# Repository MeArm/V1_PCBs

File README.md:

# V1_PCBs
Here we have the PCBs for the original controllers for the version 1 MeArm, including sliders and joysticks

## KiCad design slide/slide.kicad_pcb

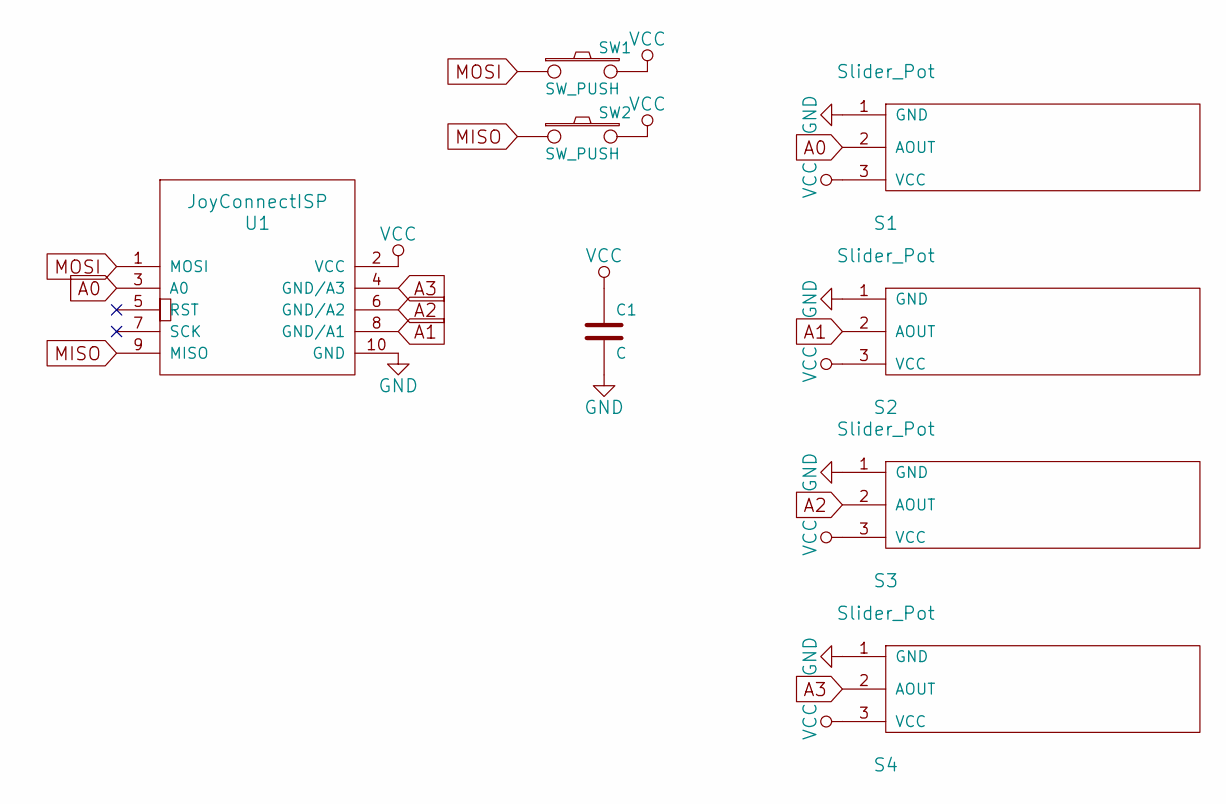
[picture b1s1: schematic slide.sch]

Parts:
C1: C; C_Disc_D3_P2.5
S1, S2, S3, S4: Slider_Pot; Slider_Potentiometer
SW1, SW2: SW_PUSH; TacSwitch
U1: JoyConnectISP; Pin_Header_Straight_2x05

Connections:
A0: S1.2 (AOUT), U1.3 (A0)
A1: S2.2 (AOUT), U1.8 (GND/A1)
A2: S3.2 (AOUT), U1.6 (GND/A2)
A3: S4.2 (AOUT), U1.4 (GND/A3)
GND: C1.2, S1.1 (GND), S2.1 (GND), S3.1 (GND), S4.1 (GND), U1.10 (GND)
MISO: SW2.1, U1.9 (MISO)
MOSI: SW1.1, U1.1 (MOSI)
VCC: C1.1, S1.3 (VCC), S2.3 (VCC), S3.3 (VCC), S4.3 (VCC), SW1.2, SW2.2, U1.2 (VCC)

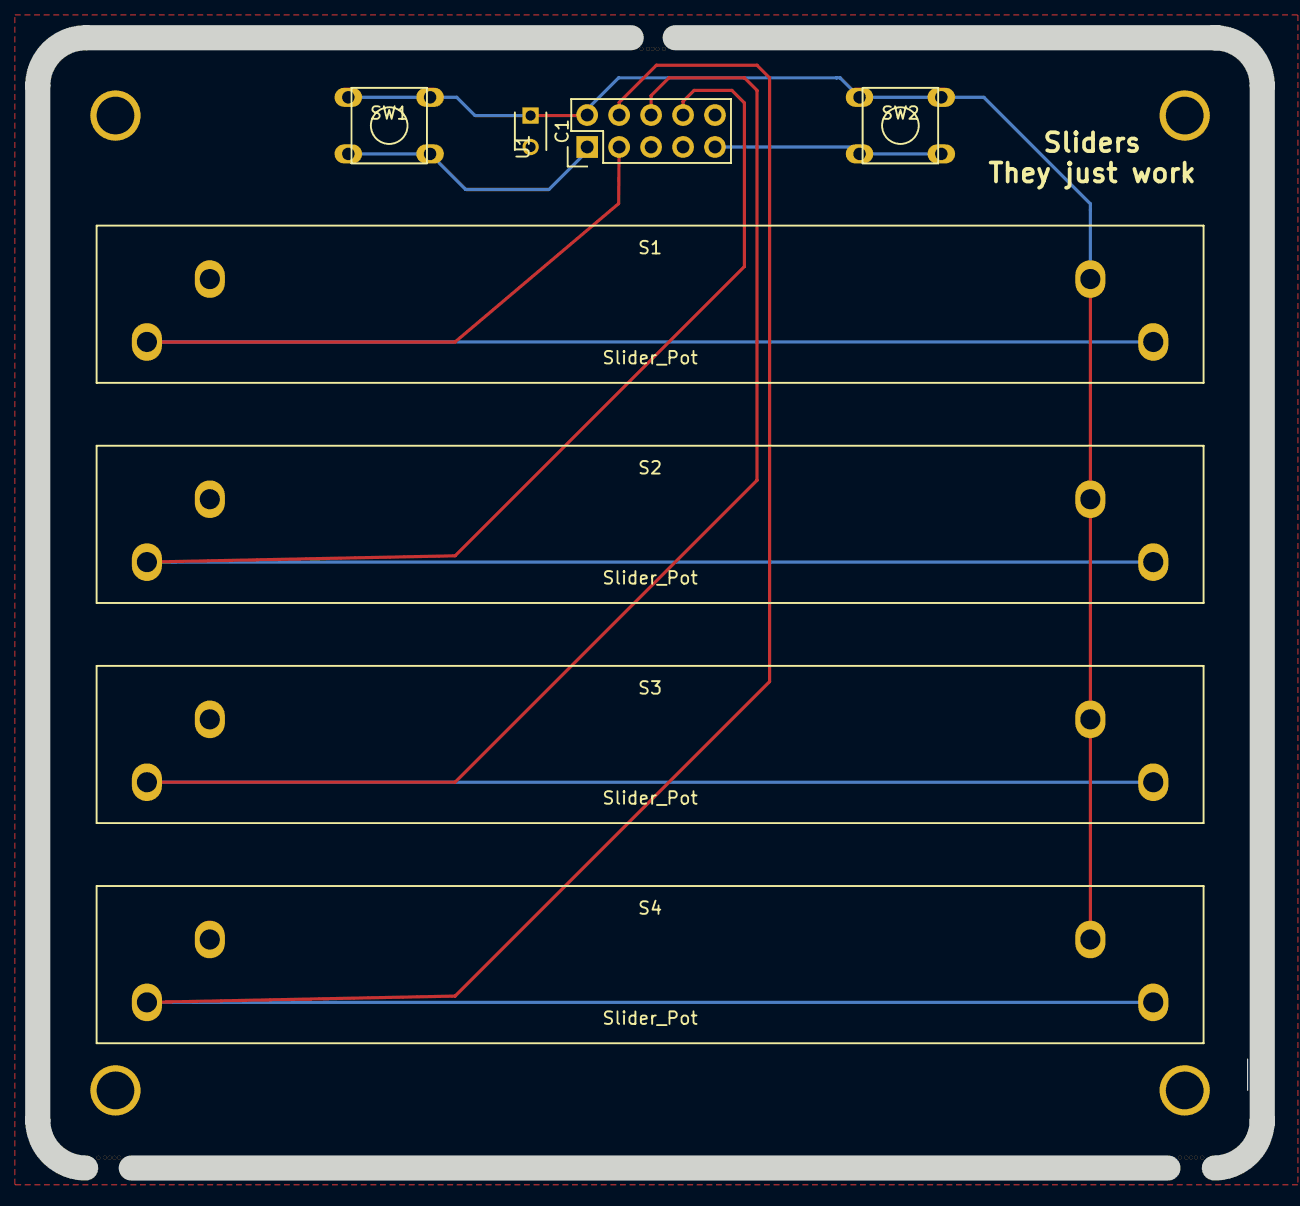
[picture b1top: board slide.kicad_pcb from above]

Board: 2 copper layers, 97.3 x 89.9 mm, 8 parts (0 on the bottom side), 8 nets.

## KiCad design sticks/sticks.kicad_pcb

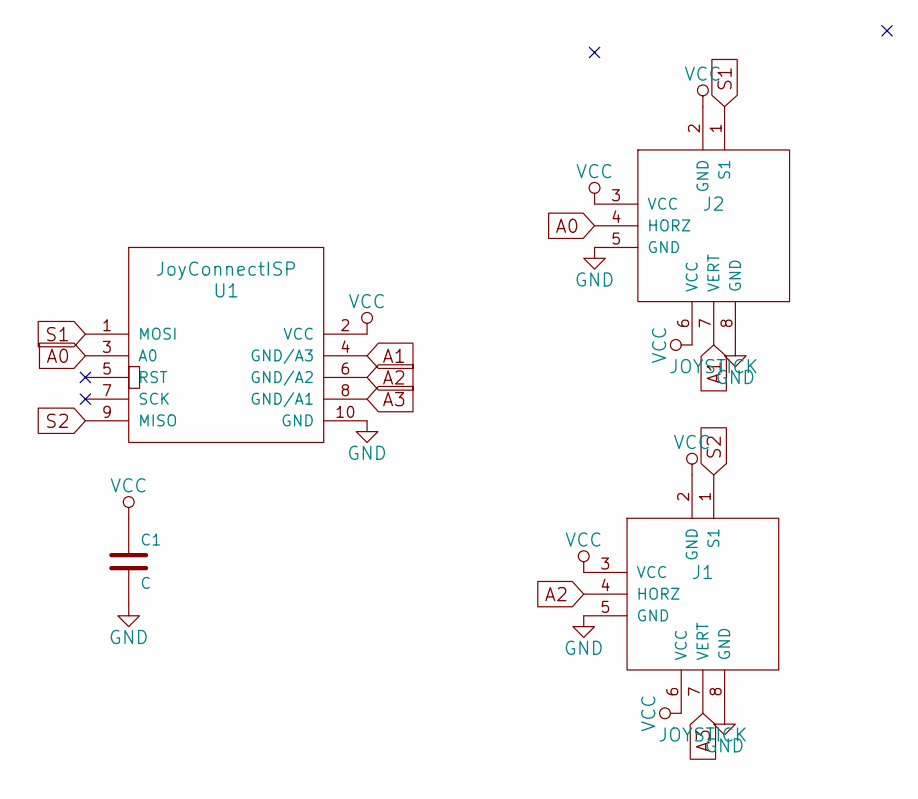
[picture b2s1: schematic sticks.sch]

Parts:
C1: C; C_Disc_D3_P2.5
J1, J2: JOYSTICK; JOYSTICKS
U1: JoyConnectISP; Pin_Header_Straight_2x05

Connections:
A0: J2.4 (HORZ), U1.3 (A0)
A1: J2.7 (VERT), U1.4 (GND/A3)
A2: J1.4 (HORZ), U1.6 (GND/A2)
A3: J1.7 (VERT), U1.8 (GND/A1)
GND: C1.2, J1.5 (GND), J1.8 (GND), J2.5 (GND), J2.8 (GND), U1.10 (GND)
S1: J2.1 (S1), U1.1 (MOSI)
S2: J1.1 (S1), U1.9 (MISO)
VCC: C1.1, J1.2 (GND), J1.3 (VCC), J1.6 (VCC), J2.2 (GND), J2.3 (VCC), J2.6 (VCC), U1.2 (VCC)

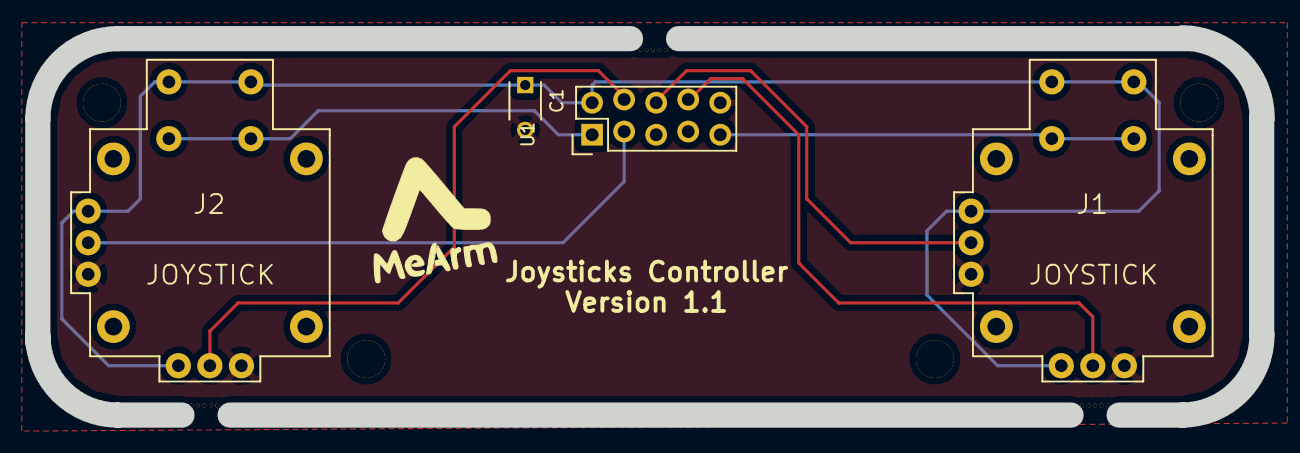
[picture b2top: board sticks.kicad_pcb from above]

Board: 2 copper layers, 97.1 x 29.9 mm, 4 parts (0 on the bottom side), 8 nets.

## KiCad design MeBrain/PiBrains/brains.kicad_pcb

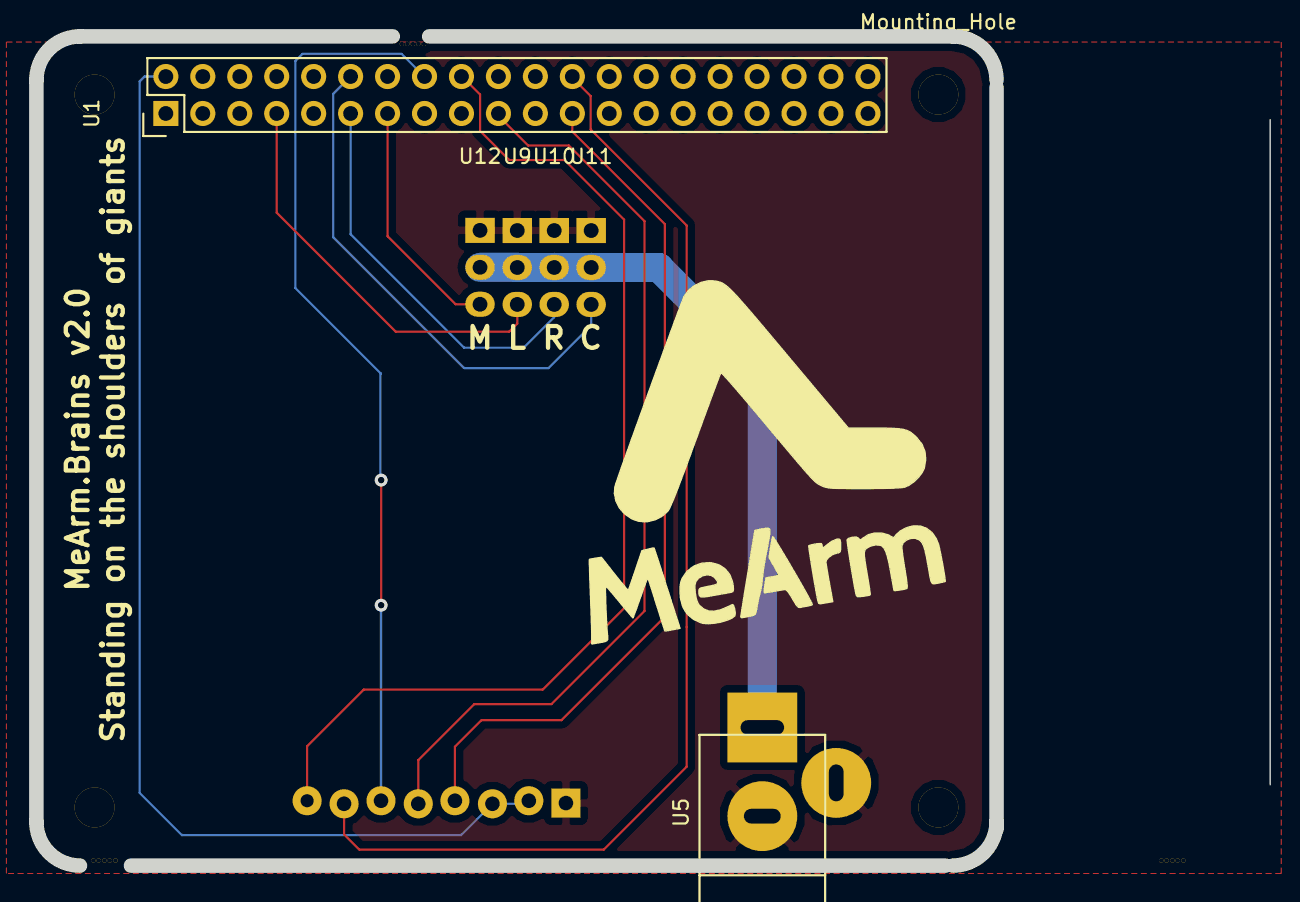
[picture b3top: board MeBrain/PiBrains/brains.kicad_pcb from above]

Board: 4 copper layers, 84.8 x 57.0 mm, 7 parts (0 on the bottom side), 6 nets.

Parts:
Mounting_Hole: Mounting_Hole
U1: PIGPIO_f; Pin_Header_Straight_2x20
U5: JACK_2MM1; JACK_ALIM
U9, U10, U11, U12: Servo; Pin_Header_Straight_1x03

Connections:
+6V: U5.1, U9.2, U10.2, U11.2, U12.2
CLAW: U1.13, U12.3
GND: U1.25, U5.2, U5.3, U9.1, U10.1, U11.1, U12.1
LEFT: U1.11, U10.3
RIGHT: U1.12, U11.3
WAIST: U1.7, U9.3

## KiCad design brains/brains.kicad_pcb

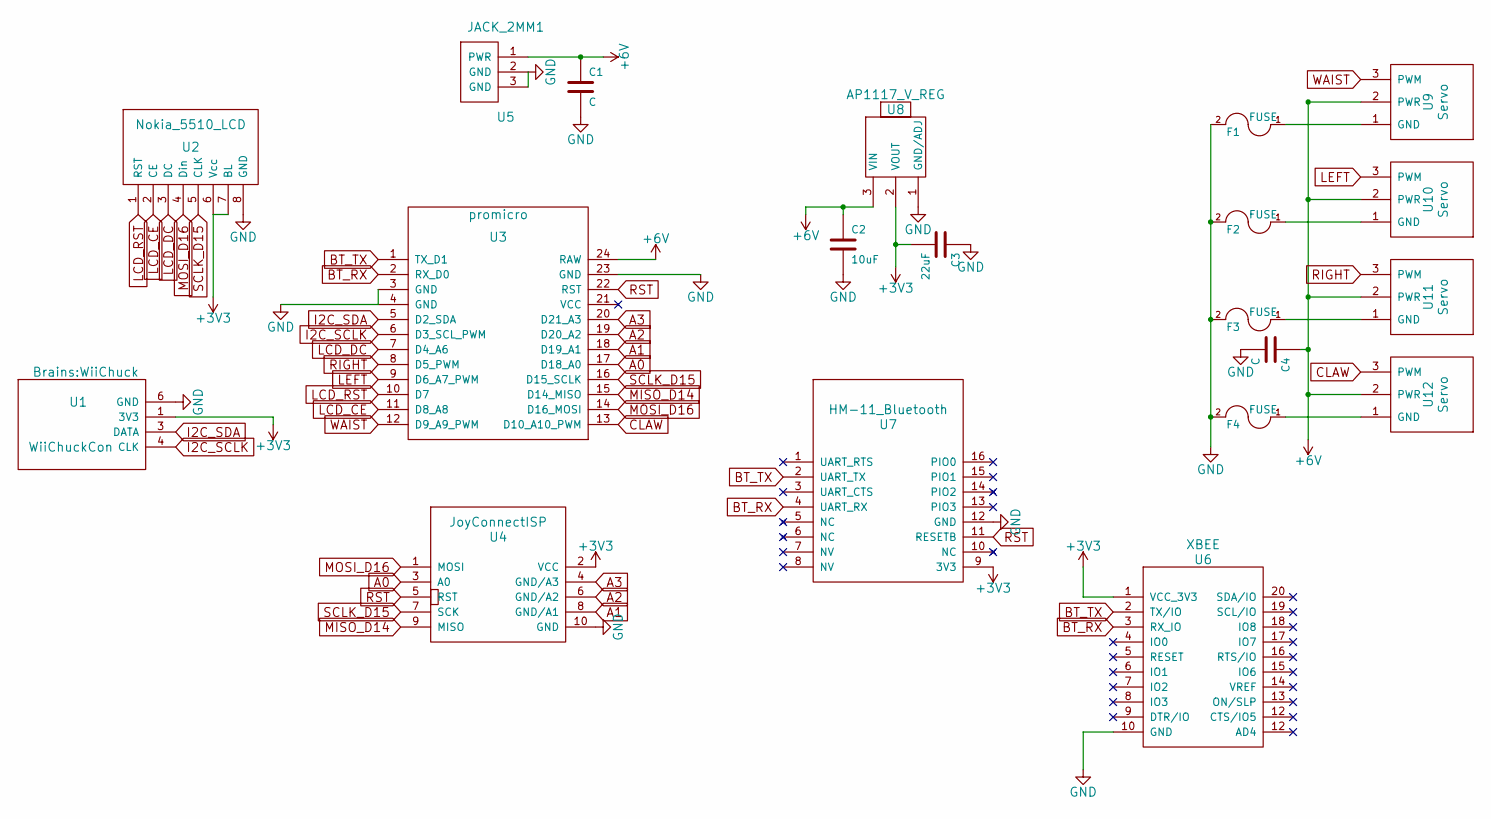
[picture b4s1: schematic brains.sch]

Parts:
C1: C; EEE1CA471UP_Capacitor
C2: 10uF; C_0805
C3: 22uF; C_1206
C4: C; C_0805
F1, F2, F3, F4: FUSE; Surface_Mount_1812_Polyfuse
U1: WiiChuckCon; WiiChuck
U2: Nokia_5510_LCD; Nokia5510LCD
U3: promicro; DIP-24__600_ELL
U4: JoyConnectISP; Pin_Header_Straight_2x05
U5: JACK_2MM1; JACK_ALIM
U6: XBEE
U7: HM-11_Bluetooth; HM-11_BT
U8: AP1117_V_REG; SOT-223
U9, U10, U11, U12: Servo; Pin_Header_Straight_1x03

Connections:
+3V3: C3.2, U1.1 (3V3), U2.6 (Vcc), U2.7 (BL), U4.2 (VCC), U6.1 (VCC_3V3), U7.9 (3V3), U8.2 (VOUT); also elsewhere on the board
+6V: C1.1, C2.1, C4.1, U3.24 (RAW), U5.1 (PWR), U8.3 (VIN), U9.2 (PWR), U10.2 (PWR), U11.2 (PWR), U12.2 (PWR)
A0: U3.17 (D18_A0), U4.3 (A0)
A1: U3.18 (D19_A1), U4.8 (GND/A1)
A2: U3.19 (D20_A2), U4.6 (GND/A2)
A3: U3.20 (D21_A3), U4.4 (GND/A3)
BT_RX: U3.2 (RX_D0), U6.3 (RX_IO), U7.4 (UART_RX); also elsewhere on the board
BT_TX: U3.1 (TX_D1), U6.2 (TX/IO), U7.2 (UART_TX); also elsewhere on the board
CLAW: U3.13 (D10_A10_PWM), U12.3 (PWM)
GND: C1.2, C2.2, C3.1, C4.2, F1.2, F2.2, F3.2, F4.2, U1.6 (GND), U2.8 (GND), U3.3 (GND), U3.4 (GND), U3.23 (GND), U4.10 (GND), U5.2 (GND), U5.3 (GND), U6.10 (GND), U7.12 (GND), U8.1 (GND/ADJ); also elsewhere on the board
I2C_SCLK: U1.4 (CLK), U3.6 (D3_SCL_PWM)
I2C_SDA: U1.3 (DATA), U3.5 (D2_SDA)
LCD_CE: U2.2 (CE), U3.11 (D8_A8)
LCD_DC: U2.3 (DC), U3.7 (D4_A6)
LCD_RST: U2.1 (RST), U3.10 (D7)
LEFT: U3.9 (D6_A7_PWM), U10.3 (PWM)
MISO_D14: U3.15 (D14_MISO), U4.9 (MISO)
MOSI_D16: U2.4 (Din), U3.14 (D16_MOSI), U4.1 (MOSI)
unnamed: F1.1, U9.1 (GND)
unnamed: F2.1, U10.1 (GND)
unnamed: F3.1, U11.1 (GND)
unnamed: F4.1, U12.1 (GND)
RIGHT: U3.8 (D5_PWM), U11.3 (PWM)
RST: U3.22 (RST), U4.5 (RST), U7.11 (RESETB)
SCLK_D15: U2.5 (CLK), U3.16 (D15_SCLK), U4.7 (SCK)
WAIST: U3.12 (D9_A9_PWM), U9.3 (PWM)

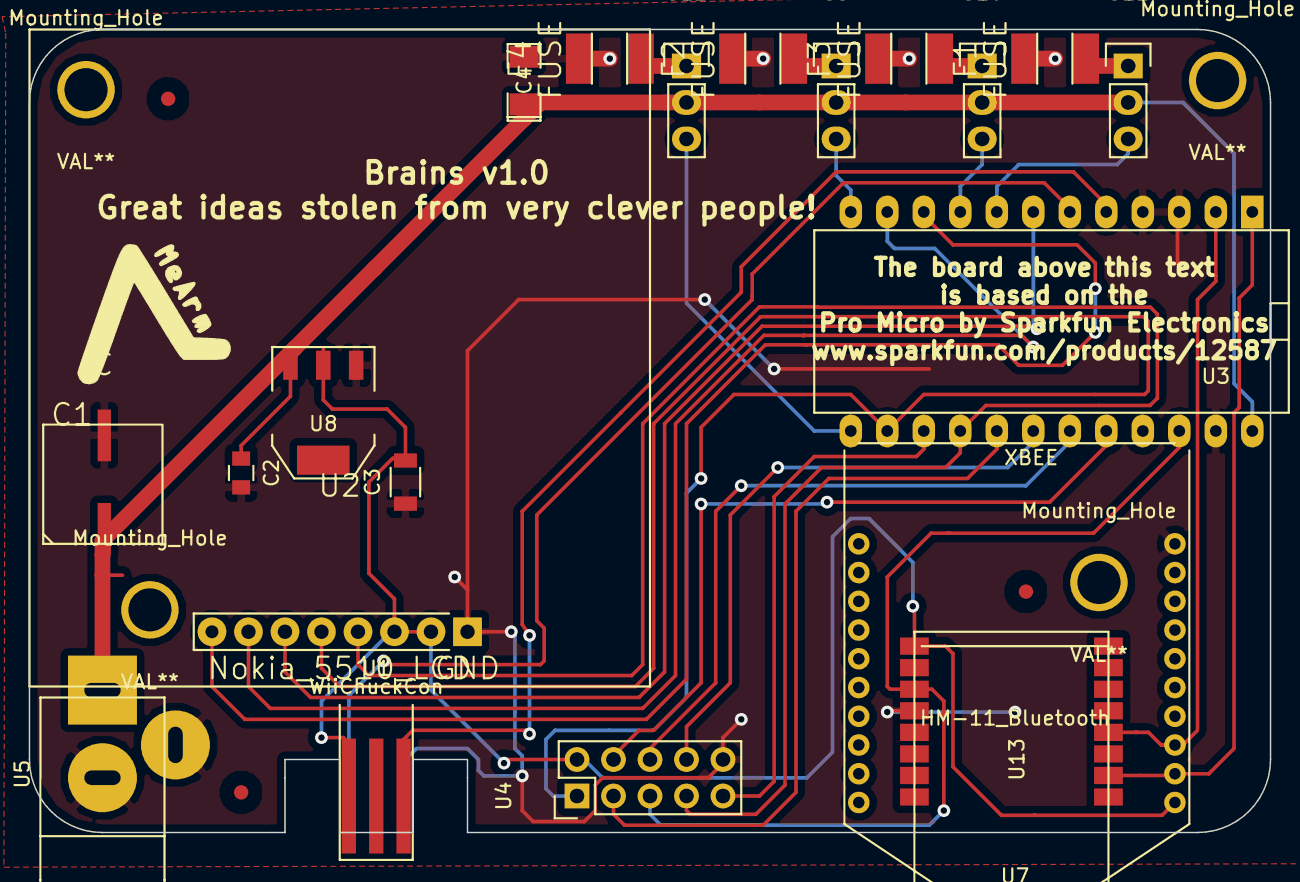
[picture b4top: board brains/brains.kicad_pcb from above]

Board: 2 copper layers, 86.4 x 55.9 mm, 24 parts (0 on the bottom side), 26 nets.

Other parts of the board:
Mounting_Hole: VAL**; Mounting_Hole
Mounting_Hole#2, Mounting_Hole#3, Mounting_Hole#4: VAL**; Mounting_Hole
U13: XBEE

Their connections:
+3V3: U13.1; also elsewhere on the board
BT_RX: U13.3; also elsewhere on the board
BT_TX: U13.2; also elsewhere on the board
GND: U13.10; also elsewhere on the board

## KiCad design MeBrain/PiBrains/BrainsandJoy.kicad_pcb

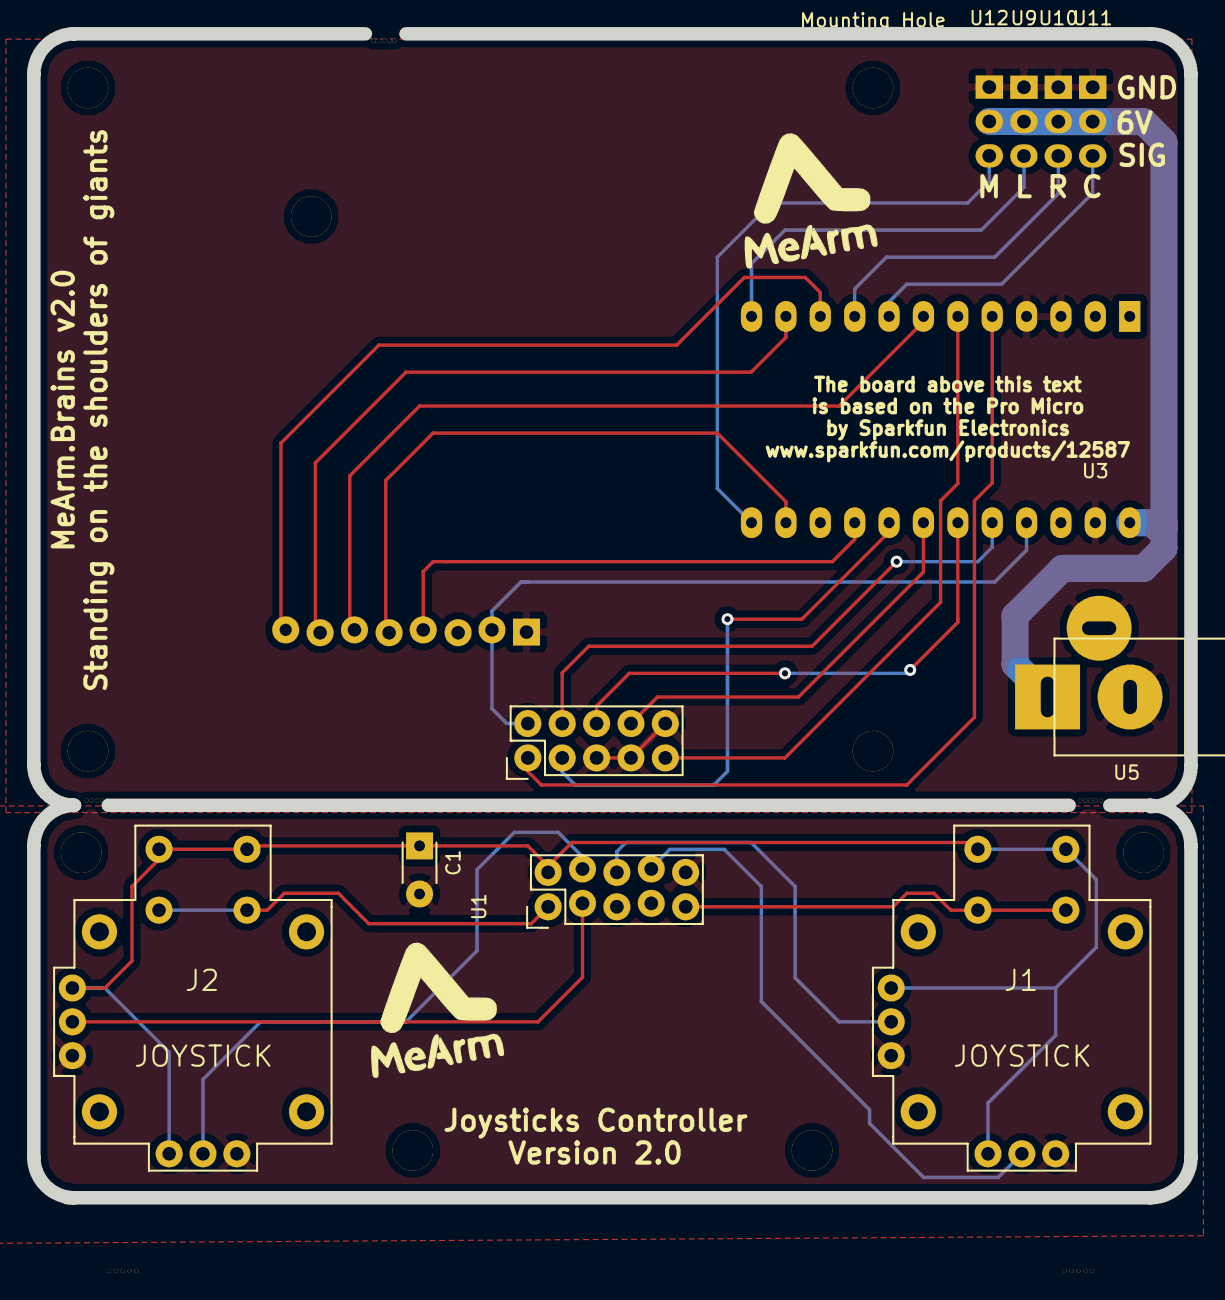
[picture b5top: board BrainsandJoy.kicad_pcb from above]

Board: 4 copper layers, 85.5 x 86.0 mm, 11 parts (0 on the bottom side), 13 nets.

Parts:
C1: C; C_Disc_D3_P2.5
J1, J2: JOYSTICK; JOYSTICKS
Mounting_Hole: Mounting_Hole
U1: JoyConnectISP; Pin_Header_Straight_2x05
U3: promicro; DIP-24__600_ELL
U5: JACK_2MM1; JACK_ALIM
U9, U10, U11, U12: Servo; Pin_Header_Straight_1x03

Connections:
+6V: U3.24, U5.1, U9.2, U10.2, U11.2, U12.2
A0: J2.4, U1.3, U3.17
A1: J2.7, U1.4, U3.18
A2: J1.4, U1.6, U3.19
A3: J1.7, U1.8, U3.20
CLAW: U3.13, U12.3
GND: C1.2, J1.5, J1.8, J2.5, J2.8, U1.10, U3.3, U3.4, U3.23, U5.2, U5.3, U9.1, U10.1, U11.1, U12.1
LEFT: U3.9, U10.3
RIGHT: U3.8, U11.3
S1: J2.1, U1.1
S2: J1.1, U1.9
VCC: C1.1, J1.2, J1.3, J1.6, J2.2, J2.3, J2.6, U1.2
WAIST: U3.12, U9.3

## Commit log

2023-10-12 all files

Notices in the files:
MeBrain/PiBrains/BrainsandJoy.kicad_pcb:
CC-BY-SA 3.0
